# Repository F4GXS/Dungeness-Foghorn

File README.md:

# Dungeness Lighthouse / St Ann's Lighthouse Foghorn Modulator
Tritone modulation of the famous Foghorn from the Dungeness Lighthouse #5 and the St Ann's Lighthouse.

The "Foghorn TriTone Modulator" is a very simple project I made to remind us of the famous and very specific tone of the foghorn.

Click this image to hear the sound.  
_Source : YouTube -  St Anns Fog Signal / "Association of Lighthouse Keepers" Channel_

Click this image to hear the sound.  
_Source : YouTube -  Dungeness 5 fog horn: 26 minutes of Tannoy fog horn / "hellooldchap" Channel_

> In 1954-56, trials had been carried out at Dungeness of a triple-frequency electric fog signal, sounded through tannoy emitters built into a curved stack of precast concrete blocks. The experiment was deemed a success, and tannoy stacks were subsequently installed by Trinity House at around a dozen lighthouse stations. At Dungeness itself, a stack of sixty such emitters was incorporated into the design of the lighthouse tower itself; these remained in use until the year 2000, when they were replaced by an electronic signal installed at the base of the tower. It sounded three blasts every minute (altered in 2022 to one blast every 30 seconds).  
_Source : [Wikipedia](https://en.wikipedia.org/wiki/Dungeness_Lighthouse)_

## Electronic Schematic

This modulator is very simple, bases on 3 NE555 Timer IC for each tone, the NE555 can easily create square wave tone with few component for tuning and each NE555 have a 5 Order LowPass Filter to transform squares waveforms tones into sines waveforms tone.

The power input voltage are 12VDC equiped with a LM7805 5VDC for the NE555.

Each channel have a multiturn potentiometer for precision frequency tuning.

The modulator are equiped with a passive inboard mixer, 3 potentiometer (1 pot for each channel, regulate the volume of each tone) and 1 for the main volume to regulate the main mix.

## Printed Circuit Board

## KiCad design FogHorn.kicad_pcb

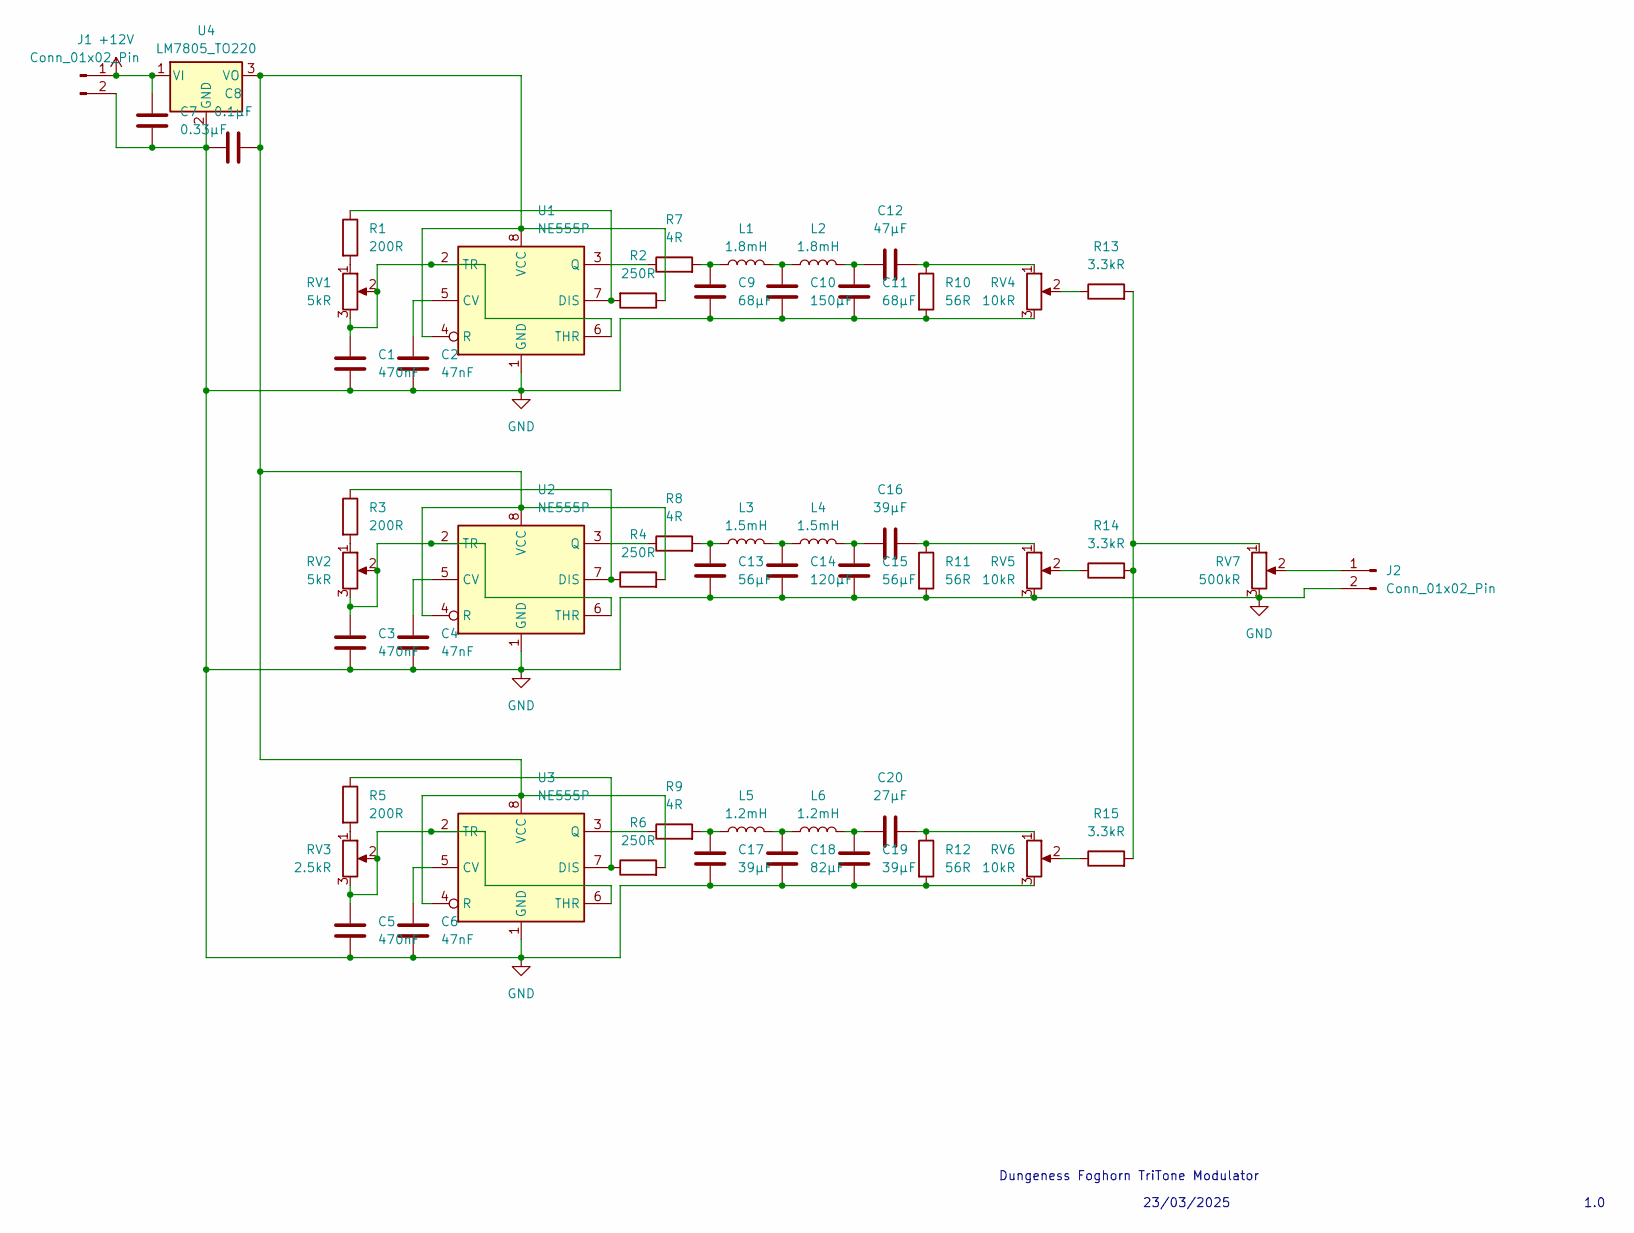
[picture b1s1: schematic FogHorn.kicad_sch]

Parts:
C1, C3, C5: 470nF; C_1206_3216Metric
C2, C4, C6: 47nF; C_1206_3216Metric
C7: 0.33µF; C_1206_3216Metric
C8: 0.1µF; C_1206_3216Metric
C9, C11: 68µF; C_1206_3216Metric
C10: 150µF; C_1206_3216Metric
C12: 47µF; C_1206_3216Metric
C13, C15: 56µF; C_1206_3216Metric
C14: 120µF; C_1206_3216Metric
C16, C17, C19: 39µF; C_1206_3216Metric
C18: 82µF; C_1206_3216Metric
C20: 27µF; C_1206_3216Metric
J1, J2: Conn_01x02_Pin; TerminalBlock_bornier-2_P5.08mm
L1, L2: 1.8mH; L_1206_3216Metric
L3, L4: 1.5mH; L_1206_3216Metric
L5, L6: 1.2mH; L_1206_3216Metric
R1, R3, R5: 200R; R_1206_3216Metric
R2, R4, R6: 250R; R_1206_3216Metric
R7, R8, R9: 4R; R_1206_3216Metric
R10, R11, R12: 56R; R_1206_3216Metric
R13, R14, R15: 3.3kR; R_1206_3216Metric
RV1, RV2: 5kR; Potentiometer_Bourns_3266W_Vertical
RV3: 2.5kR; Potentiometer_Bourns_3266W_Vertical
RV4, RV5, RV6: 10kR; Potentiometer_ACP_CA9-V10_Vertical
RV7: 500kR; Potentiometer_ACP_CA9-V10_Vertical
U1, U2, U3: NE555P; DIP-8_W7.62mm
U4: LM7805_TO220; TO-220-3_Vertical

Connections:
+12V: C7.1, J1.1, U4.1 (VI)
GND: C1.2, C2.2, C3.2, C4.2, C5.2, C6.2, C7.2, C8.1, C9.2, C10.2, C11.2, C13.2, C14.2, C15.2, C17.2, C18.2, C19.2, J1.2, J2.2, R10.2, R11.2, R12.2, RV4.3, RV5.3, RV6.3, RV7.3, U1.1 (GND), U2.1 (GND), U3.1 (GND), U4.2 (GND)
unnamed: C9.1, L1.1, R7.2
unnamed: C10.1, L1.2, L2.1
unnamed: C11.1, C12.1, L2.2
unnamed: C12.2, R10.1, RV4.1
unnamed: C13.1, L3.1, R8.2
unnamed: C14.1, L3.2, L4.1
unnamed: C15.1, C16.1, L4.2
unnamed: C16.2, R11.1, RV5.1
unnamed: C17.1, L5.1, R9.2
unnamed: C18.1, L5.2, L6.1
unnamed: C19.1, C20.1, L6.2
unnamed: C20.2, R12.1, RV6.1
unnamed: J2.1, RV7.2
unnamed: R1.2, RV1.1
unnamed: R3.2, RV2.1
unnamed: R5.2, RV3.1
unnamed: R13.1, RV4.2
unnamed: R13.2, R14.2, R15.2, RV7.1
unnamed: R14.1, RV5.2
unnamed: R15.1, RV6.2
unnamed: C2.1, U1.5 (CV)
unnamed: R1.1, R2.2, U1.7 (DIS)
unnamed: R7.1, U1.3 (Q)
unnamed: C8.2, R2.1, R4.2, R6.2, U1.4 (R), U1.8 (VCC), U2.4 (R), U2.8 (VCC), U3.4 (R), U3.8 (VCC), U4.3 (VO)
unnamed: C1.1, RV1.2, RV1.3, U1.2 (TR), U1.6 (THR)
unnamed: C4.1, U2.5 (CV)
unnamed: R3.1, R4.1, U2.7 (DIS)
unnamed: R8.1, U2.3 (Q)
unnamed: C3.1, RV2.2, RV2.3, U2.2 (TR), U2.6 (THR)
unnamed: C6.1, U3.5 (CV)
unnamed: R5.1, R6.1, U3.7 (DIS)
unnamed: R9.1, U3.3 (Q)
unnamed: C5.1, RV3.2, RV3.3, U3.2 (TR), U3.6 (THR)

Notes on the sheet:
Dungeness Foghorn TriTone Modulator
1.0
23/03/2025

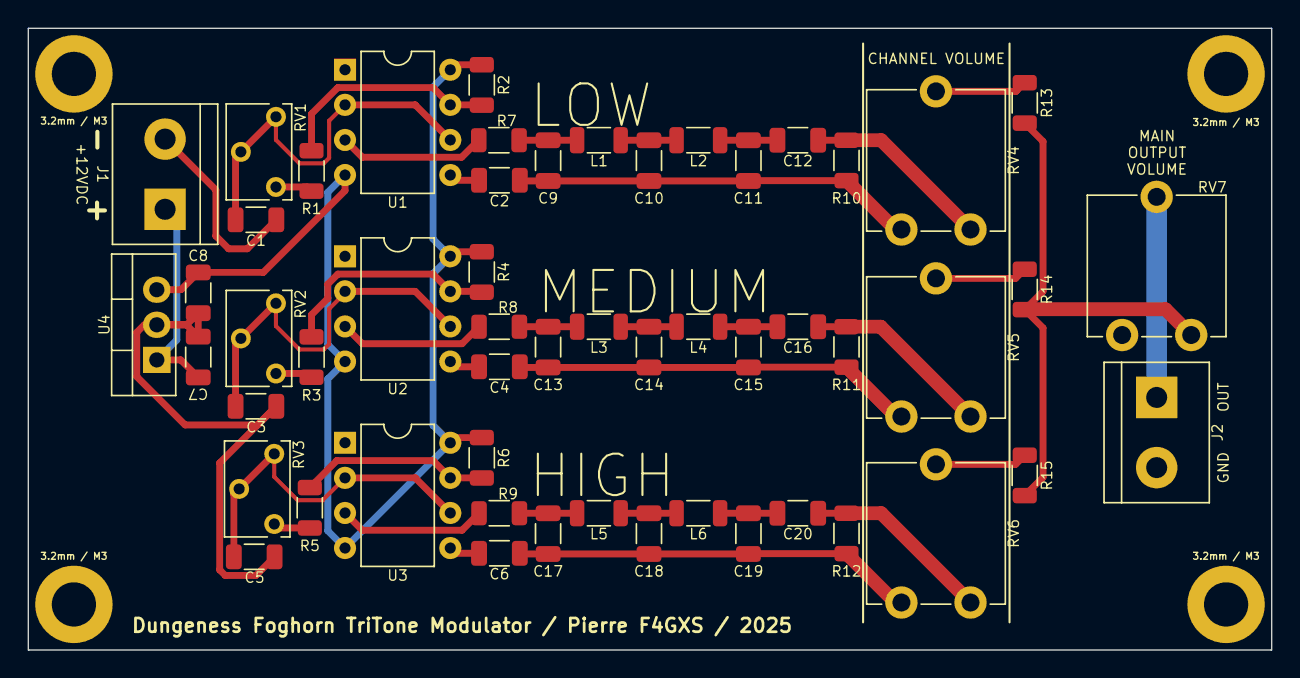
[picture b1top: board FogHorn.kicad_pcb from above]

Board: 2 copper layers, 90.0 x 45.0 mm, 58 parts (0 on the bottom side), 35 nets.

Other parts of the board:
3.2mm / M3, 3.2mm / M3#2, 3.2mm / M3#3, 3.2mm / M3#4: MountingHole_3.2mm_M3_DIN965_Pad

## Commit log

2025-03-29 Adding Kicad project files
